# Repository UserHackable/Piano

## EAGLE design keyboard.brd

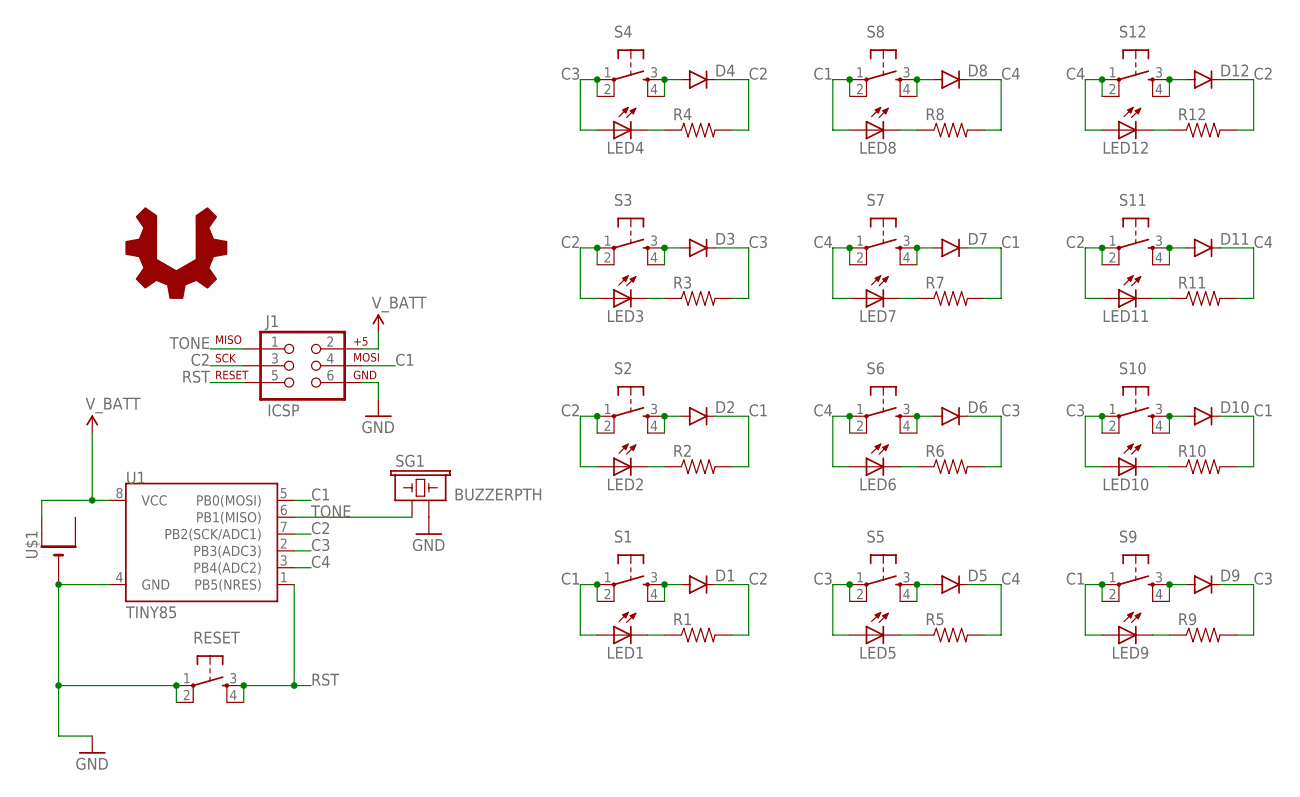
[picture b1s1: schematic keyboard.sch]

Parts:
D1, D2, D3, D4, D5, D6, D7, D8, D9, D10, D11, D12: DIODE1N4148; DIODE-1N4148
J1: ICSP; 2X3-NS
LED1, LED2, LED3, LED4, LED5, LED6, LED7, LED8, LED9, LED10, LED11, LED12: LED5MM
R1, R2, R3, R4, R5, R6, R7, R8, R9, R10, R11, R12: RESISTORAXIAL-0.3; AXIAL-0.3
RESET: TAC_SWITCHPTH; TACTILE-PTH
S1, S2, S3, S4, S5, S6, S7, S8, S9, S10, S11, S12: TAC_SWITCHPTH; TACTILE-PTH
SG1: BUZZERPTH; BUZZER-12MM
U1: TINY85; DIP08
U$1: CR2032THM; CR2032-THRU
U$2: USER_HACKABLE

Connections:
C1: D2.C, D7.C, D10.C, J1.4 (MOSI), LED1.A, LED8.A, LED9.A, R2.P$2 (2), R7.P$2 (2), R10.P$2 (2), S1.1, S1.2, S8.1, S8.2, S9.1, S9.2, U1.5 (PB0(MOSI))
C2: D1.C, D4.C, D12.C, J1.3 (SCK), LED2.A, LED3.A, LED11.A, R1.P$2 (2), R4.P$2 (2), R12.P$2 (2), S2.1, S2.2, S3.1, S3.2, S11.1, S11.2, U1.7 (PB2(SCK/ADC1))
C3: D3.C, D6.C, D9.C, LED4.A, LED5.A, LED10.A, R3.P$2 (2), R6.P$2 (2), R9.P$2 (2), S4.1, S4.2, S5.1, S5.2, S10.1, S10.2, U1.2 (PB3(ADC3))
C4: D5.C, D8.C, D11.C, LED6.A, LED7.A, LED12.A, R5.P$2 (2), R8.P$2 (2), R11.P$2 (2), S6.1, S6.2, S7.1, S7.2, S12.1, S12.2, U1.3 (PB4(ADC2))
GND: J1.6 (GND), RESET.1, RESET.2, SG1.- (2), U1.4 (GND), U$1.-
unnamed: LED1.K (C), R1.P$1 (1)
unnamed: D1.A, S1.3, S1.4
unnamed: LED2.K (C), R2.P$1 (1)
unnamed: D2.A, S2.3, S2.4
unnamed: LED3.K (C), R3.P$1 (1)
unnamed: D3.A, S3.3, S3.4
unnamed: LED4.K (C), R4.P$1 (1)
unnamed: D4.A, S4.3, S4.4
unnamed: LED5.K (C), R5.P$1 (1)
unnamed: D5.A, S5.3, S5.4
unnamed: LED6.K (C), R6.P$1 (1)
unnamed: D6.A, S6.3, S6.4
unnamed: LED7.K (C), R7.P$1 (1)
unnamed: D7.A, S7.3, S7.4
unnamed: LED8.K (C), R8.P$1 (1)
unnamed: D8.A, S8.3, S8.4
unnamed: LED9.K (C), R9.P$1 (1)
unnamed: D9.A, S9.3, S9.4
unnamed: LED10.K (C), R10.P$1 (1)
unnamed: D10.A, S10.3, S10.4
unnamed: LED11.K (C), R11.P$1 (1)
unnamed: D11.A, S11.3, S11.4
unnamed: LED12.K (C), R12.P$1 (1)
unnamed: D12.A, S12.3, S12.4
RST: J1.5 (RST), RESET.3, RESET.4, U1.1 (PB5(NRES))
TONE: J1.1 (MISO), SG1.+ (1), U1.6 (PB1(MISO))
V_BATT: J1.2 (V+), U1.8 (VCC), U$1.+1 (+)

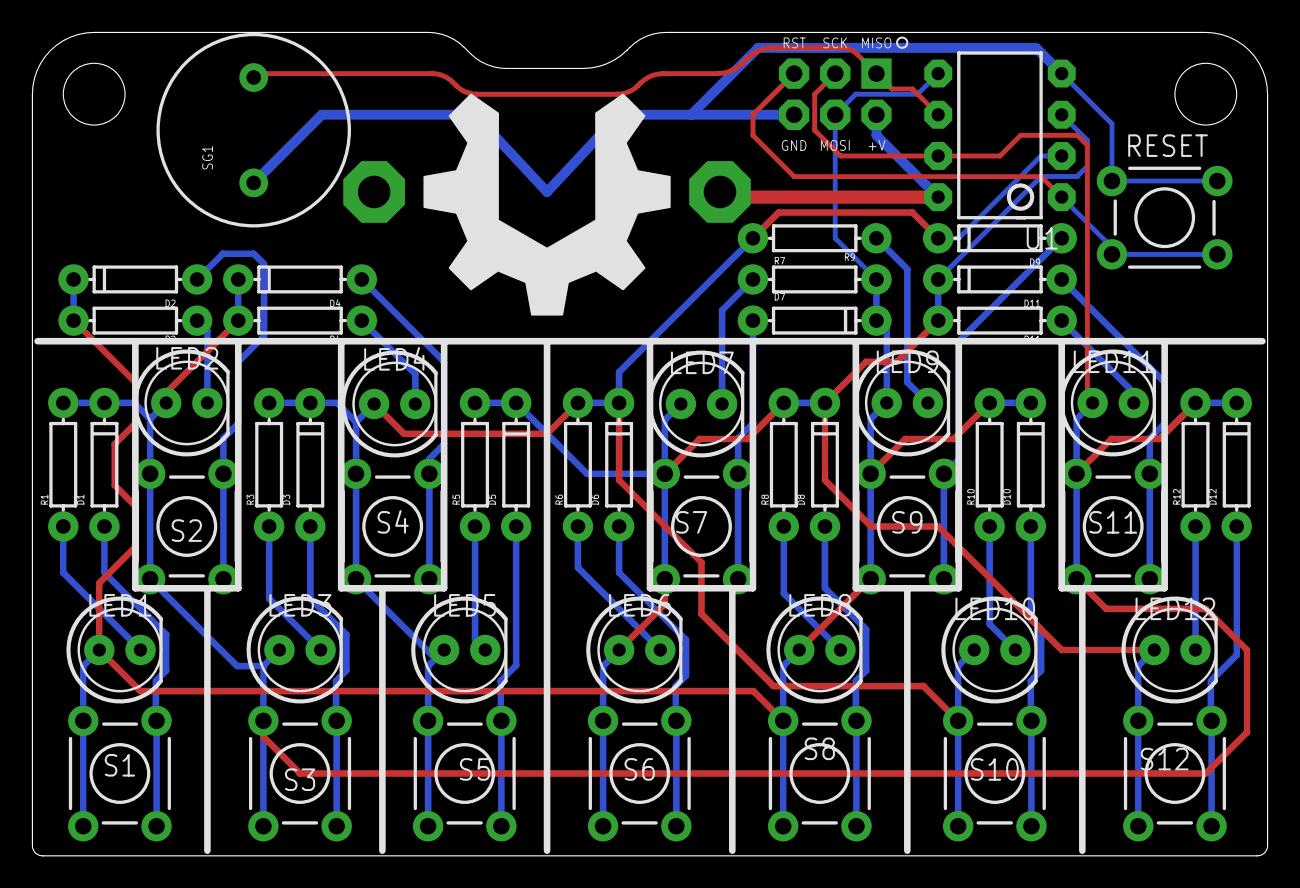
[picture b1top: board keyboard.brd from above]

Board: 2 copper layers, 76.2 x 50.8 mm, 54 parts (1 on the bottom side), 32 nets.

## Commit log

2016-04-07 from Makefile

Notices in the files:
parts and their libraries:
SparkFun-DiscreteSemi: Licensing: Creative Commons ShareAlike 4.0 International - https://creativecommons.org/licenses/by-sa/4.0
